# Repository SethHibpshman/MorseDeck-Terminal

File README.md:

# MorseDeck Terminal

> A standalone Morse code keyer and trainer built on the ESP32-S3, featuring real-time decoding, four keying modes, a rotary settings menu, and T9-style keyboard replay.

<p align="center">
  
</p>

<p align="center">
  <a href="https://youtu.be/P0Hb8axpHqs">▶️ Watch the Full Demo</a>
</p>

> Full build documentation, hardware reference, and software notes are in the [project wiki](../../wiki). For an account of the technical challenges, design decisions, and lessons learned, see [Design Reflections](../../wiki/5.-Design-Reflections).

## Table of Contents

- [Overview](#overview)
- [Functionality](#functionality)
  - [Operating Modes](#operating-modes)
  - [Keying Modes](#keying-modes)
  - [Morse Decoding](#morse-decoding)
  - [Keyboard Replay Mode](#keyboard-replay-mode)
  - [Settings Menu](#settings-menu)
- [System Design](#system-design)
  - [Hardware](#hardware)
  - [PCB Design](#pcb-design)
  - [Software](#software)
- [Bill of Materials](#bill-of-materials)
- [Author](#author)
- [AI Disclosure](#ai-disclosure)
- [License](#license)

## Overview

MorseDeck Terminal is a fully self-contained Morse code keyer and trainer built on the ESP32-S3 and programmed in MicroPython. The device supports professional-grade iambic keying with automatic real-time decoding, a rotary encoder settings interface, multi-tap keyboard input, and serial output to an external display, all running on a custom PCB in a 3D-printed enclosure.

The project was designed and built from scratch for **EENG 163: Introduction to Embedded Systems** at Eastern Washington University, covering real-time signal generation, hardware input handling, OLED display rendering, and inter-device communication.

## Functionality

### Operating Modes

The device has three selectable operating modes, accessible from the settings menu:

| Mode | Description |
|---|---|
| **Sandbox** | Free-form keying with live decoding on the OLED |
| **Keyboard Replay** | Type text via keypad and play it back as Morse |
| **Debug** | Live readout of paddle state, encoder pins, keypad input, and memory |

### Keying Modes

Four keying styles are supported, covering both traditional and modern paddle techniques:

| Mode | Behavior |
|---|---|
| **Iambic A** | Alternates dit/dah while both paddles are held; stops on release |
| **Iambic B** | Same as A, but sends one extra element after both paddles are released |
| **Ultimatic** | Last-pressed paddle wins when both are held simultaneously |
| **Straight Key** | Either paddle held produces a continuous tone |

### Morse Decoding

Gap detection runs automatically in the background and scales with the live WPM setting:

- After **3x the dit duration** of paddle idle time, a letter space is inserted and the buffered sequence is decoded to the OLED
- After **7x the dit duration**, the space is upgraded to a word break

### Keyboard Replay Mode

Text can be entered using the 4x4 keypad with T9-style multi-tap input, following a standard phone keyboard layout. The device encodes the typed text to Morse in real time, displays it on the OLED, and plays it back through the buzzer on command.

| Key | Action |
|---|---|
| A | Backspace |
| B | Play current text as Morse |

### Settings Menu

Hold the rotary encoder button for **2 seconds** to open the settings menu. Short-press to enter edit mode on any item, then rotate to adjust.

| Setting | Options |
|---|---|
| Mode | Sandbox, Keyboard Replay, Debug |
| Keying Mode | Iambic A, Iambic B, Ultimatic, Straight Key |
| Volume | 0-10 |
| LED | Enabled / Disabled |
| Decoding | Enabled / Disabled |
| About | Scrolling credits page |
| Reset | Hard resets the device |

Additional behaviors include a typewriter-style boot screen on startup and a bouncing-logo screensaver after 60 seconds of inactivity.

## System Design

### Hardware

| Component | Details |
|---|---|
| Microcontroller | ESP32-S3 |
| Display | SSD1306 128x64 OLED (SoftI2C) |
| Paddles | 2x momentary buttons (Dit / Dah) |
| Keypad | 4x4 membrane matrix keypad |
| Rotary Encoder | CLK, DT, SW with long-press menu activation |
| Buzzer | Piezo PWM buzzer |
| LED | Single external indicator LED |

> Full pin mapping and wiring notes are in the [Hardware Reference](../../wiki/3.-Hardware-Reference) wiki page.

### PCB Design

Designed in KiCad. All project files are in [`/hardware/kicad_project_files`](/hardware/kicad_project_files).

### Software

Written entirely in **MicroPython** as a single-file application.

**Dependencies:** `ssd1306`, `gfx`, `keypad`, `urandom`

```
main.py    # Full application: hardware init, all functions, main loop
```

> Code structure, dependencies, and configuration details are in the [Software Reference](../../wiki/4.-Software-Reference) wiki page.

## Bill of Materials

| Item | Qty | Unit | Total |
|---|---|---|---|
| [ESP32-S3 Dev Board](https://a.co/d/08OKpdB2) | 1 | $6.40 | $6.40 |
| SSD1306 OLED 128x64 | 1 | $3.00 | $3.00 |
| Rotary Encoder | 1 | $3.00 | $3.00 |
| 4x4 Membrane Keypad | 1 | $1.60 | $1.60 |
| PCBs | 1 | - | $5.00 |
| Piezo Buzzer (Active) | 1 | $0.35 | $0.35 |
| Resistors | - | - | $0.12 |
| LED | 1 | $0.03 | $0.03 |
| 3D-printed enclosure | 1 | - | $0.00 |
| **Grand Total** | | | **$19.50** |

> - Unit costs reflect bulk purchasing; individual retail prices may be higher.
> - 3D printing assumes university or personal printer access.
> - PCB cost assumes overseas fabrication.

## Author

**Seth Hibpshman**  
Student of Electrical Engineering, Eastern Washington University

## AI Disclosure
_AI (LLM) tools were used for quality assurance review of the firmware and in the drafting and editing of this README and wiki documentation; all code was written by hand._

## License

[GNU General Public License v3.0](LICENSE)

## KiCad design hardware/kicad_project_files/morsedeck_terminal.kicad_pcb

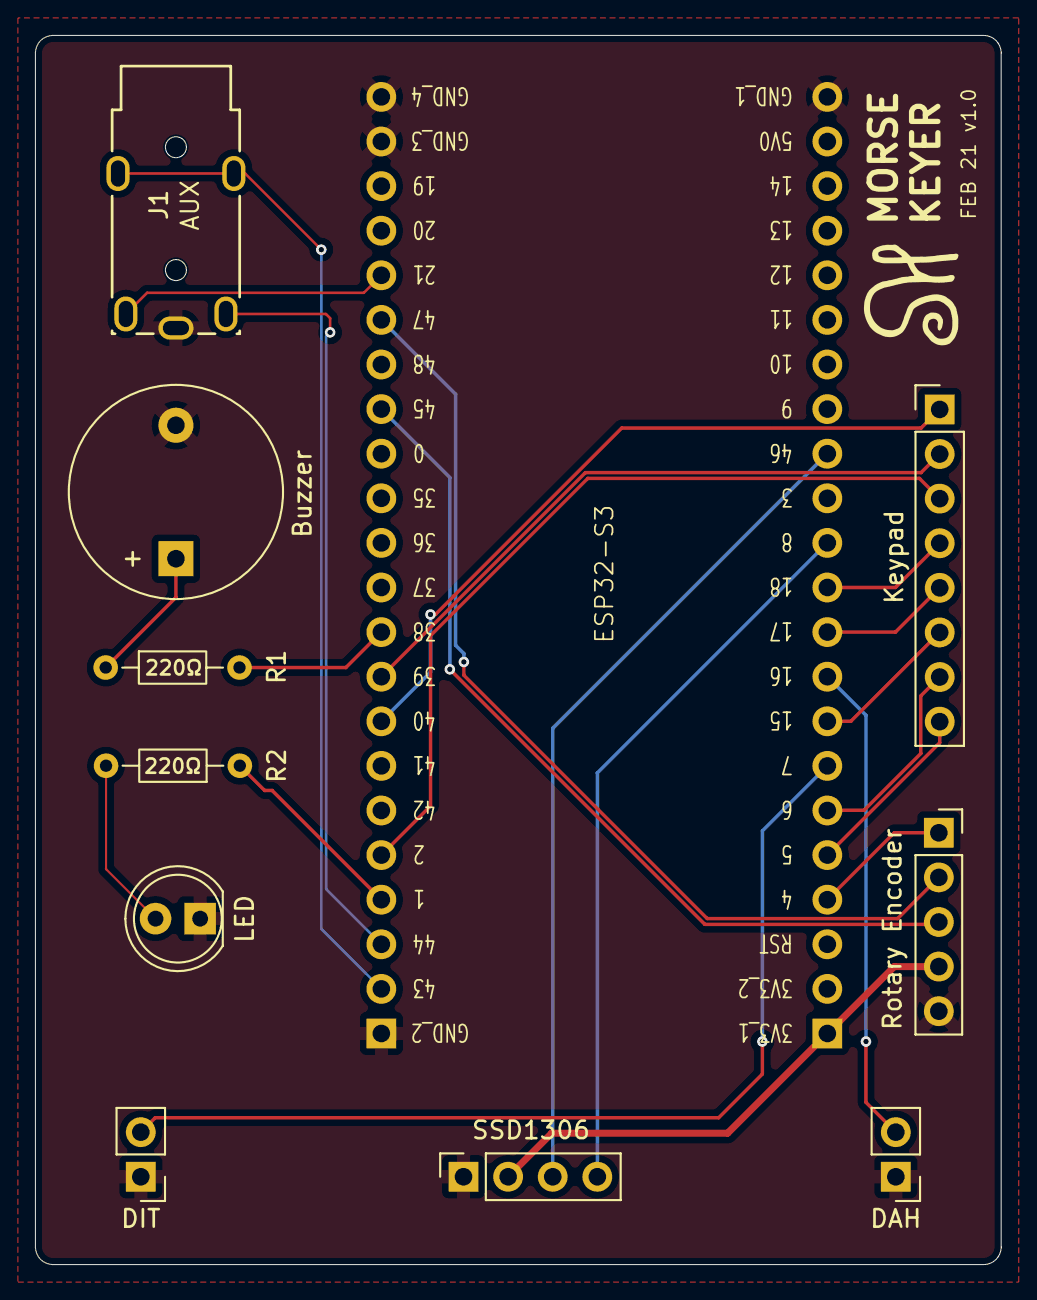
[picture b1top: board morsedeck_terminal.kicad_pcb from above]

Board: 4 copper layers, 55.0 x 70.0 mm, 11 parts (0 on the bottom side), 24 nets.

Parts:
Buzzer: Buzzer_12x9.5RM7.6
DAH: SW_Push; PinHeader_1x02_P2.54mm_Vertical
DIT: SW_Push; PinHeader_1x02_P2.54mm_Vertical
ESP32-S3: ESP32-S3 Mount
J1: 3.5mm Aux Jack; 54-00174_TEN
Keypad: PinHeader_1x08_P2.54mm_Vertical
LED: LED; LED_D5.0mm
R1, R2: R_US; R_Axial_DIN0204_L3.6mm_D1.6mm_P7.62mm_Horizontal
Rotary Encoder: PinSocket_1x05_P2.54mm_Vertical
SSD1306: PinSocket_1x04_P2.54mm_Vertical

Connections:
+3V3: ESP32-S3.3V3_1 (3V3), Rotary Encoder.4 (+), SSD1306.2 (VCC)
/GPIO1: ESP32-S3.1 (GPIO1), R2.1
/GPIO2: ESP32-S3.2 (GPIO2), Keypad.3 (Col_2)
/GPIO4: ESP32-S3.4 (GPIO4), Rotary Encoder.1 (CLK)
/GPIO5: ESP32-S3.5 (GPIO5), Keypad.8 (Row_1)
/GPIO6: ESP32-S3.6 (GPIO6), Keypad.7 (Row_2)
/GPIO7: DIT.2, ESP32-S3.7 (GPIO7)
/GPIO8: ESP32-S3.8 (GPIO8), SSD1306.4 (SDA)
/GPIO15: ESP32-S3.15 (GPIO15), Keypad.6 (Row_3)
/GPIO16: DAH.2, ESP32-S3.16 (GPIO16)
/GPIO17: ESP32-S3.17 (GPIO17), Keypad.5 (Row_4)
/GPIO18: ESP32-S3.18 (GPIO18), Keypad.4 (Col_1)
/GPIO21: ESP32-S3.21 (GPIO21), J1.1 (Sleeve_SW)
/GPIO38: ESP32-S3.38 (GPIO38), R1.2
/GPIO39: ESP32-S3.39 (GPIO39), Keypad.2 (Col_3)
/GPIO40: ESP32-S3.40 (GPIO40), Keypad.1 (Col_4)
/GPIO45: ESP32-S3.45 (GPIO45), Rotary Encoder.3 (SW)
/GPIO46: ESP32-S3.46 (GPIO46), SSD1306.3 (SCL)
/GPIO47: ESP32-S3.47 (GPIO47), Rotary Encoder.2 (DT)
/RX/GPIO44: ESP32-S3.44 (RX/GPIO44), J1.3 (Ring)
/TX/GPIO43: ESP32-S3.43 (TX/GPIO43), J1.4 (Tip)
GND: Buzzer.2 (-), DAH.1, DIT.1, ESP32-S3.GND_1 (GND), ESP32-S3.GND_2 (GND), ESP32-S3.GND_3 (GND), ESP32-S3.GND_4 (GND), J1.2 (Sleeve), LED.1 (K), Rotary Encoder.5 (GND), SSD1306.1 (GND)
unnamed: Buzzer.1 (+), R1.1
unnamed: LED.2 (A), R2.2

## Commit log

2026-06-14 Morse Keyer ---> MorseDeck Terminal Rebrand
    Rebranded all Morse Keyer titles to MorseDeck Terminal.
    Removed stm32 telegraph features.
    Reorganized project folder structure.
2026-06-14 Removed divider lines
2026-06-14 Organized Assets
2026-06-14 Updated README Image Links
2026-06-14 Update image links
2026-06-14 Enclosure files
2026-06-14 New cover image
2026-06-14 Add paddles
